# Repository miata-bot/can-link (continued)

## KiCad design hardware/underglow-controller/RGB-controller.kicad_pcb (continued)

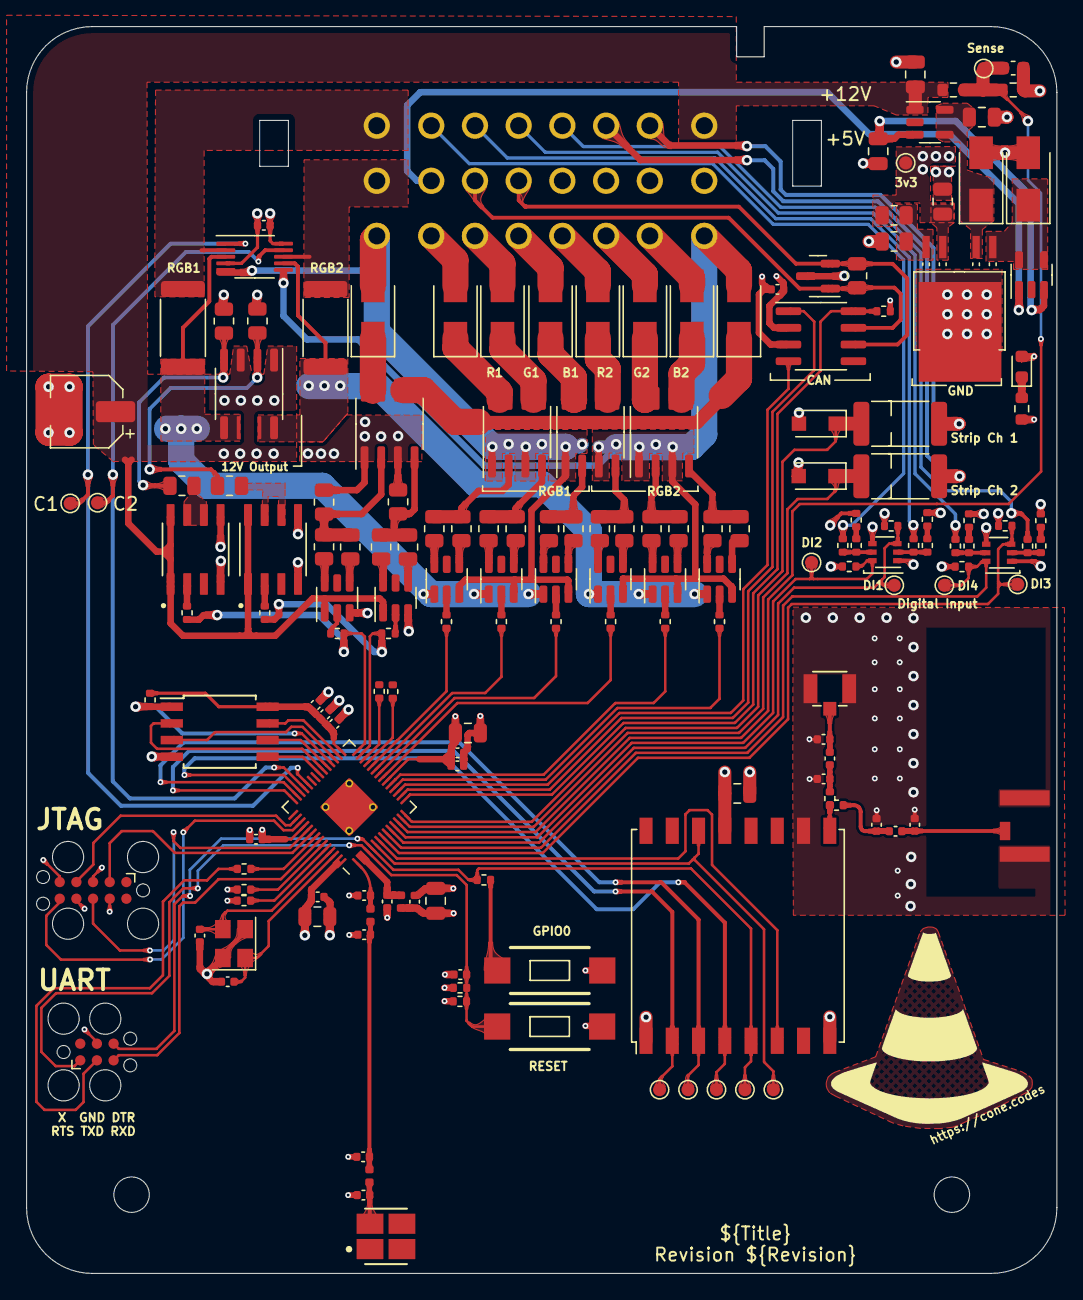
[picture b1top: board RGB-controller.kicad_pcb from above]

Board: 4 copper layers, 78.5 x 95.0 mm, 172 parts (0 on the bottom side), 140 nets.

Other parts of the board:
Enclosure_Bottom: Enclosure_Bottom
Enclosure_Top: Enclosure_Top

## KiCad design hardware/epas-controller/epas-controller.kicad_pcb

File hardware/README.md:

# Hardware Design

Here you'll find the hub for all the sub projects and KiCAD libraries.

| Folder | Description |
| -------| ----------- |
| [`underglow-controller`](/hardware/underglow-controller/README.md) | RGB controller board |
| - | - |
| [`library`](/hardware/library/README.md) | Library of KiCAD Parts |

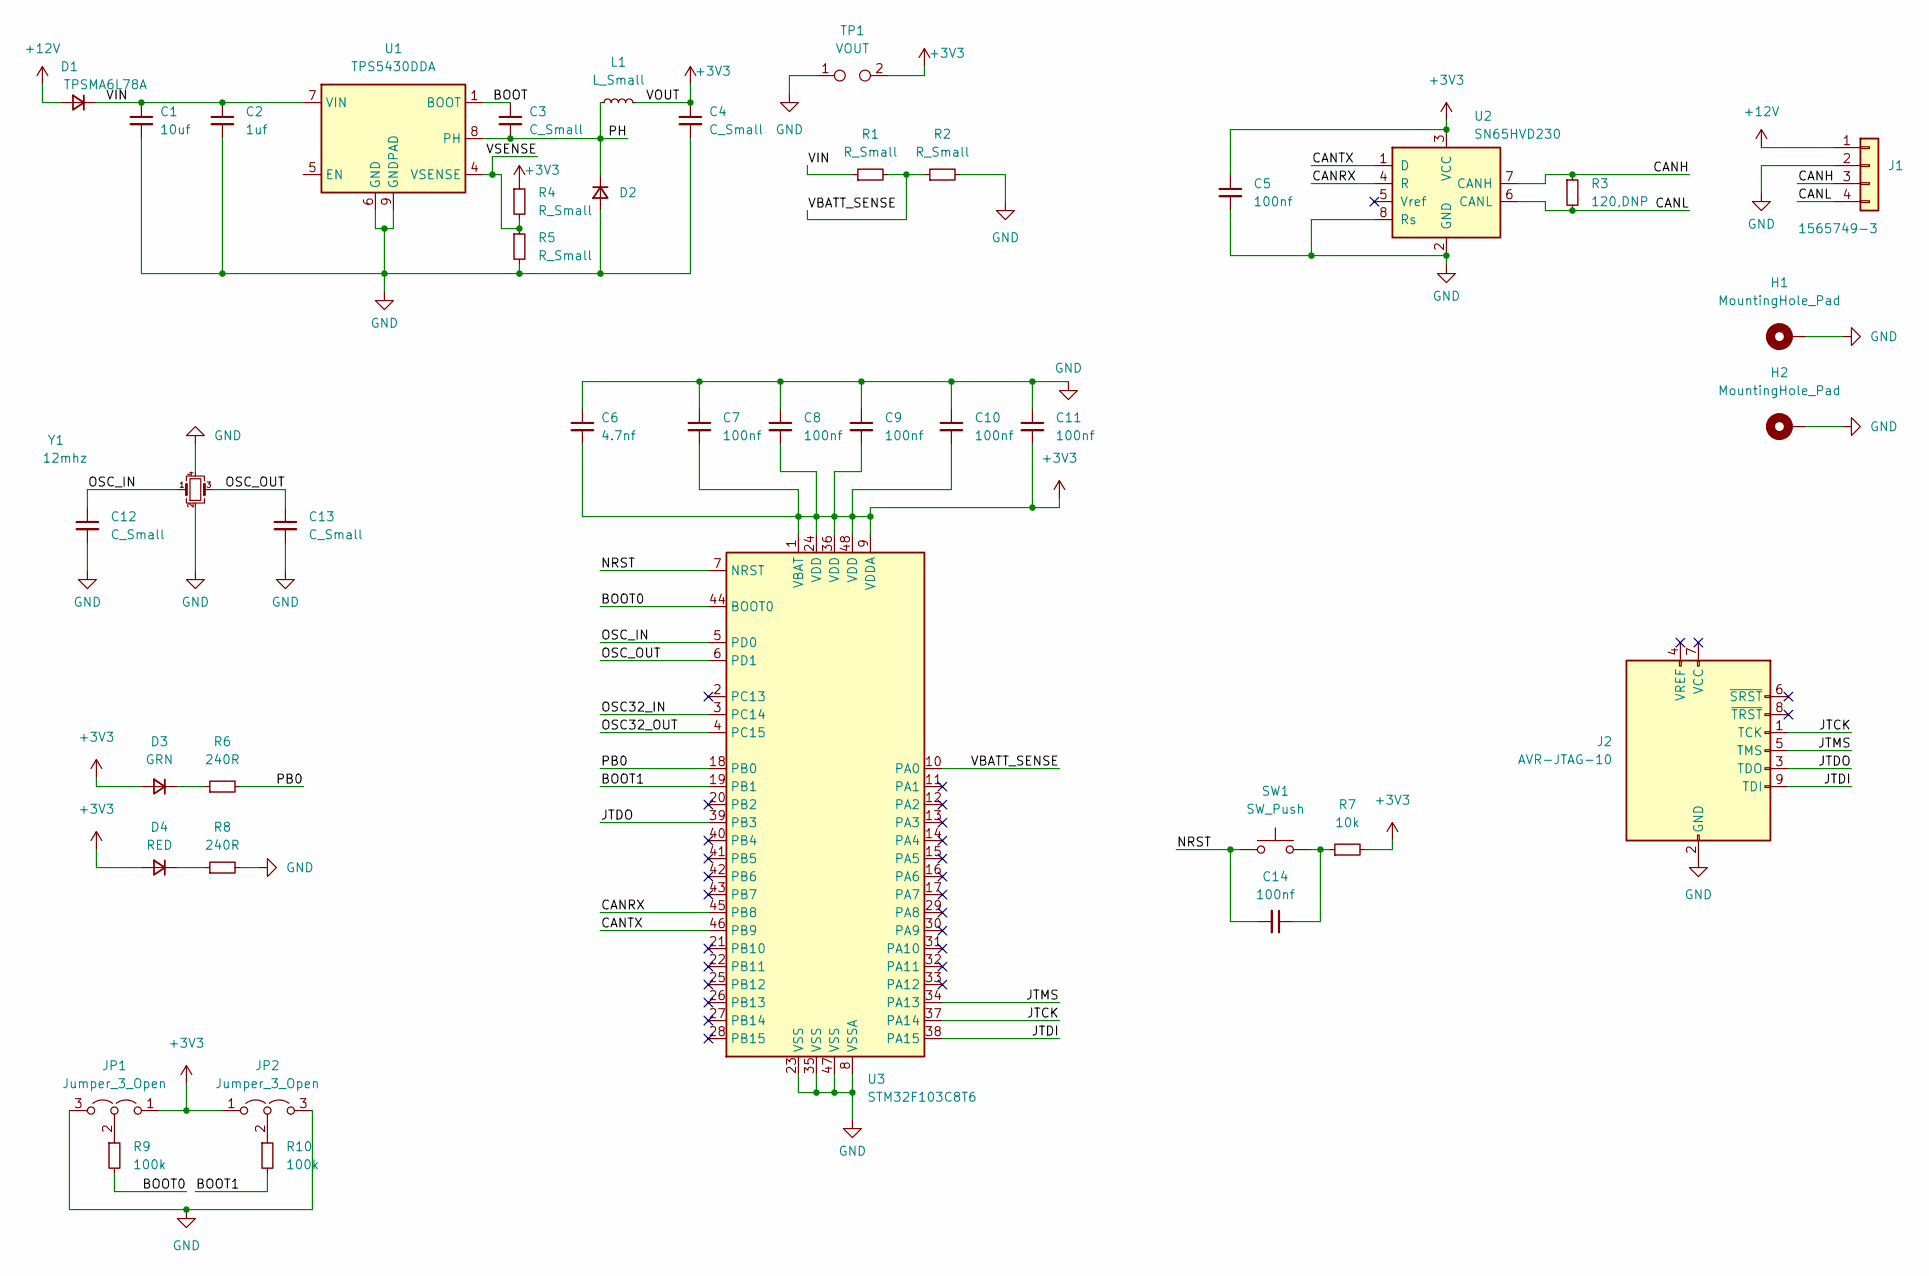
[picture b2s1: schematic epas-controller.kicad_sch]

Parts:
C1: 10uf; C_0805_2012Metric
C2: 1uf; C_0805_2012Metric
C3, C4: C_Small; C_0805_2012Metric
C5, C7, C8, C9, C10, C11, C14: 100nf; C_0402_1005Metric
C6: 4.7nf; C_0805_2012Metric
C12, C13: C_Small; C_0402_1005Metric
D1: TPSMA6L78A; D_SMA; MPN TPSMA6L78A
D2: D_Small; D_SOD-123F; MPN CUHS15S30,H3F
D3: GRN; LED_0603_1608Metric
D4: RED; LED_0603_1608Metric
H1, H2: MountingHole_Pad; MountingHole_3.2mm_M3_Pad_Via
J1: 1565749-3
J2: AVR-JTAG-10; PinHeader_2x06_P1.27mm_Vertical_SMD
JP1, JP2: Jumper_3_Open; SolderJumper-3_P1.3mm_Open_Pad1.0x1.5mm_NumberLabels
L1: L_Small; L_Bourns-SRN6028
R1, R2, R4, R5: R_Small; R_0603_1608Metric
R3: 120,DNP; R_0805_2012Metric
R6, R8: 240R; R_0603_1608Metric
R7: 10k; R_0402_1005Metric
R9, R10: 100k; R_0402_1005Metric
SW1: SW_Push; SW_RS-032G05A3-SMRT
TP1: VOUT; TestPoint_2Pads_Pitch2.54mm_Drill0.8mm
U1: TPS5430DDA; TI_SO-PowerPAD-8_ThermalVias; LCSC C9864
U2: SN65HVD230; SOIC-8_3.9x4.9mm_P1.27mm
U3: STM32F103C8T6; LQFP-48_7x7mm_P0.5mm; LCSC STM32F103C8T6
Y1: 12mhz; Crystal_SMD_3225-4Pin_3.2x2.5mm; MPN 12MHz SMD Crystal Resonator 20pF ±10ppm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; LCSC C9002

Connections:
+3V3: C4.1, C5.1, C6.2, C7.2, C8.2, C9.2, C10.2, C11.2, D3.2 (A), D4.2 (A), JP1.1 (A), JP2.1 (A), L1.2, R4.1, R7.2, TP1.2, U2.3 (VCC), U3.1 (VBAT), U3.9 (VDDA), U3.24 (VDD), U3.36 (VDD), U3.48 (VDD)
+12V: D1.2 (A), J1.1
/BOOT: C3.1, U1.1 (BOOT)
/BOOT0: R9.2, U3.44 (BOOT0)
/BOOT1: R10.2, U3.19 (PB1)
/CANH: J1.3, R3.1, U2.7 (CANH)
/CANL: J1.4, R3.2, U2.6 (CANL)
/CANRX: U2.4 (R), U3.45 (PB8)
/CANTX: U2.1 (D), U3.46 (PB9)
/JTCK: J2.1 (TCK), U3.37 (PA14)
/JTDI: J2.9 (TDI), U3.38 (PA15)
/JTDO: J2.3 (TDO), U3.39 (PB3)
/JTMS: J2.5 (TMS), U3.34 (PA13)
/NRST: C14.2, SW1.1, U3.7 (NRST)
/OSC32_IN: U3.3 (PC14)
/OSC32_OUT: U3.4 (PC15)
/OSC_IN: C12.1, U3.5 (PD0), Y1.1
/OSC_OUT: C13.1, U3.6 (PD1), Y1.3
/PB0: R6.2, U3.18 (PB0)
/PH: C3.2, D2.1 (K), L1.1, U1.8 (PH)
/VBATT_SENSE: R1.2, R2.1, U3.10 (PA0)
/VIN: C1.1, C2.1, D1.1 (K), R1.1, U1.7 (VIN)
/VSENSE: R4.2, R5.1, U1.4 (VSENSE)
GND: C1.2, C2.2, C4.2, C5.2, C6.1, C7.1, C8.1, C9.1, C10.1, C11.1, C12.2, C13.2, D2.2 (A), H1.1, H2.1, J1.2, J2.2 (GND), J2.10 (GND), JP1.3 (B), JP2.3 (B), R2.2, R5.2, R8.2, TP1.1, U1.6 (GND), U1.9 (GNDPAD), U2.2 (GND), U2.8 (Rs), U3.8 (VSSA), U3.23 (VSS), U3.35 (VSS), U3.47 (VSS), Y1.2, Y1.4
unnamed: C14.1, R7.1, SW1.2
unnamed: D3.1 (K), R6.1
unnamed: D4.1 (K), R8.1
unnamed: JP1.2 (C), R9.1
unnamed: JP2.2 (C), R10.1

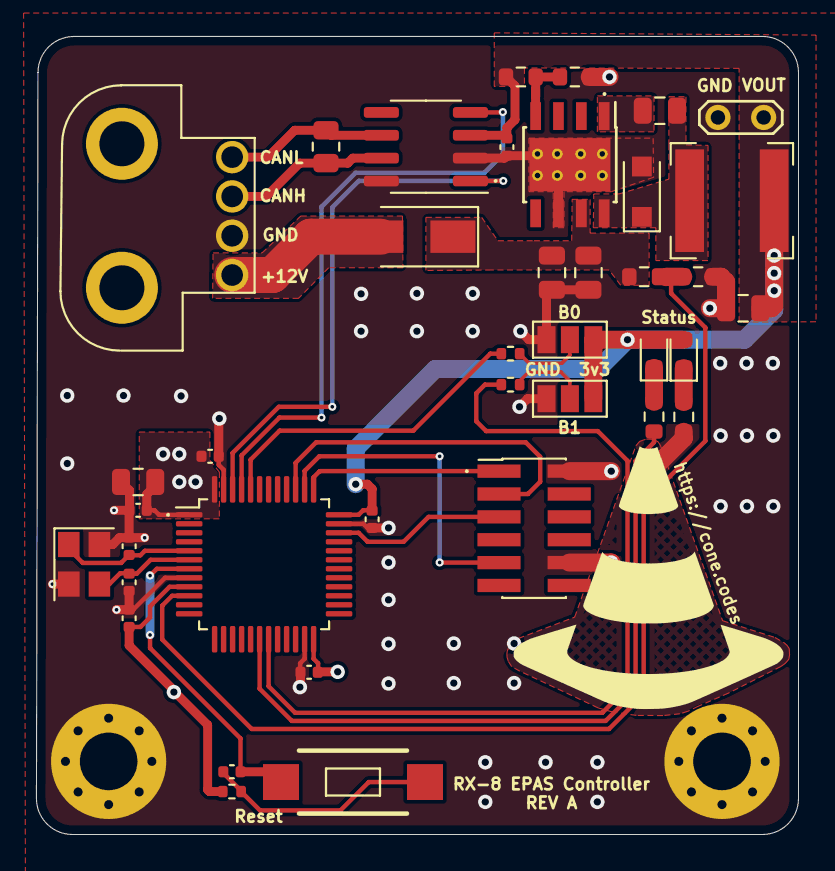
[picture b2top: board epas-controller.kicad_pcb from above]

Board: 2 copper layers, 42.3 x 44.3 mm, 41 parts (0 on the bottom side), 27 nets.

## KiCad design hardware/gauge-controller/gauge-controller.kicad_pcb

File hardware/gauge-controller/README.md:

# CAN Multi-Gauge Controller

Device designed to display information from an ECU?

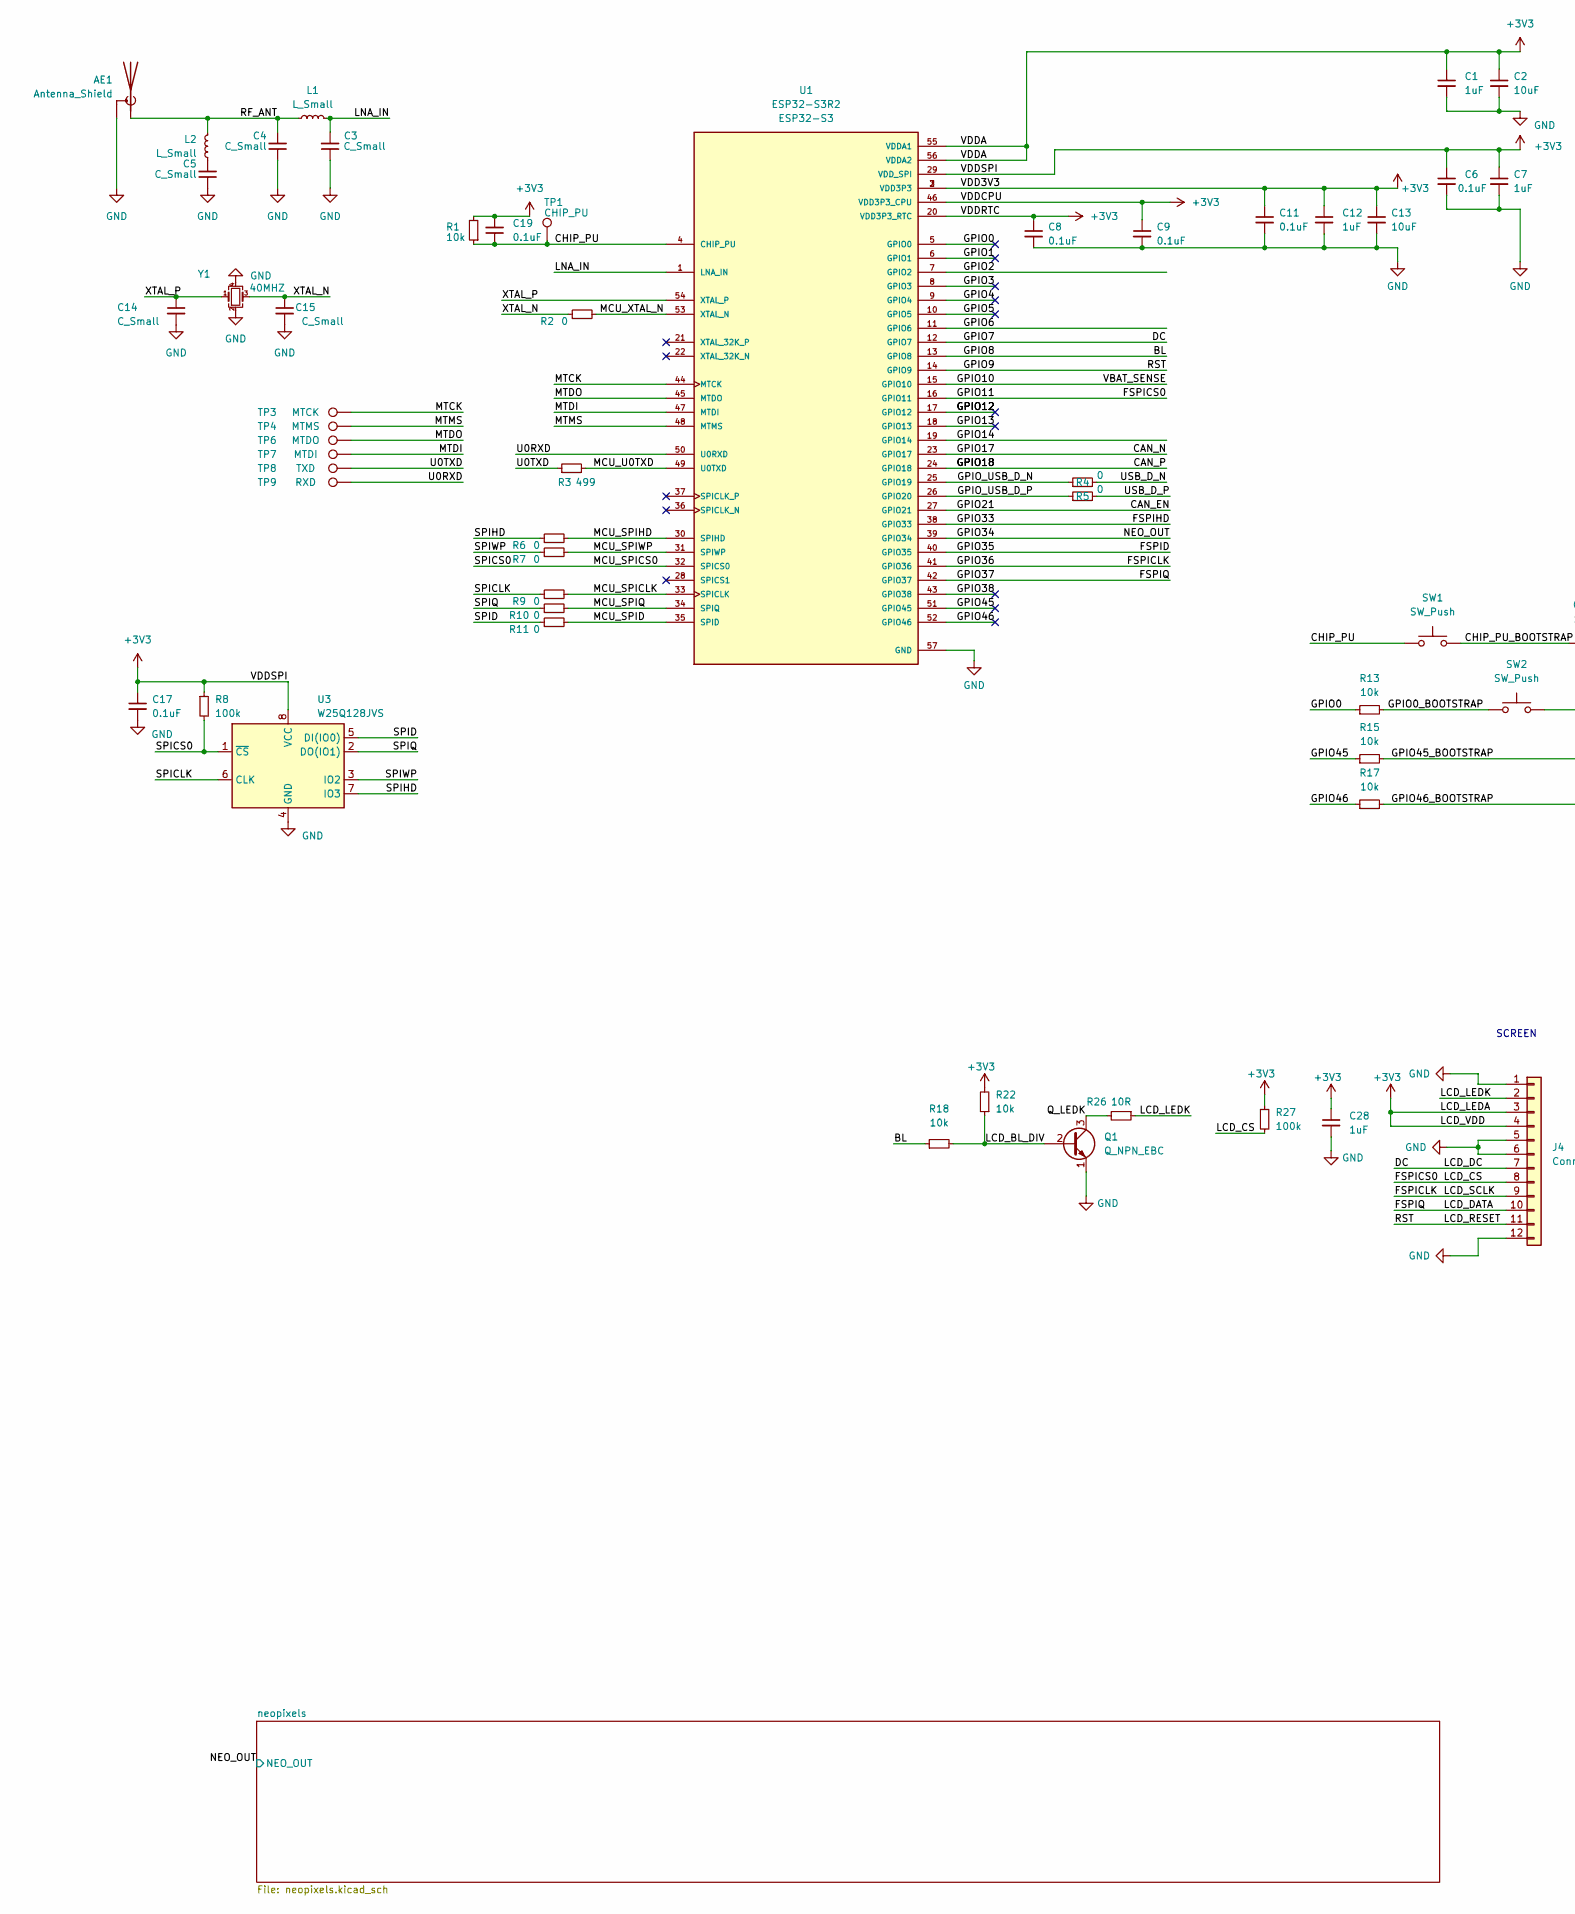
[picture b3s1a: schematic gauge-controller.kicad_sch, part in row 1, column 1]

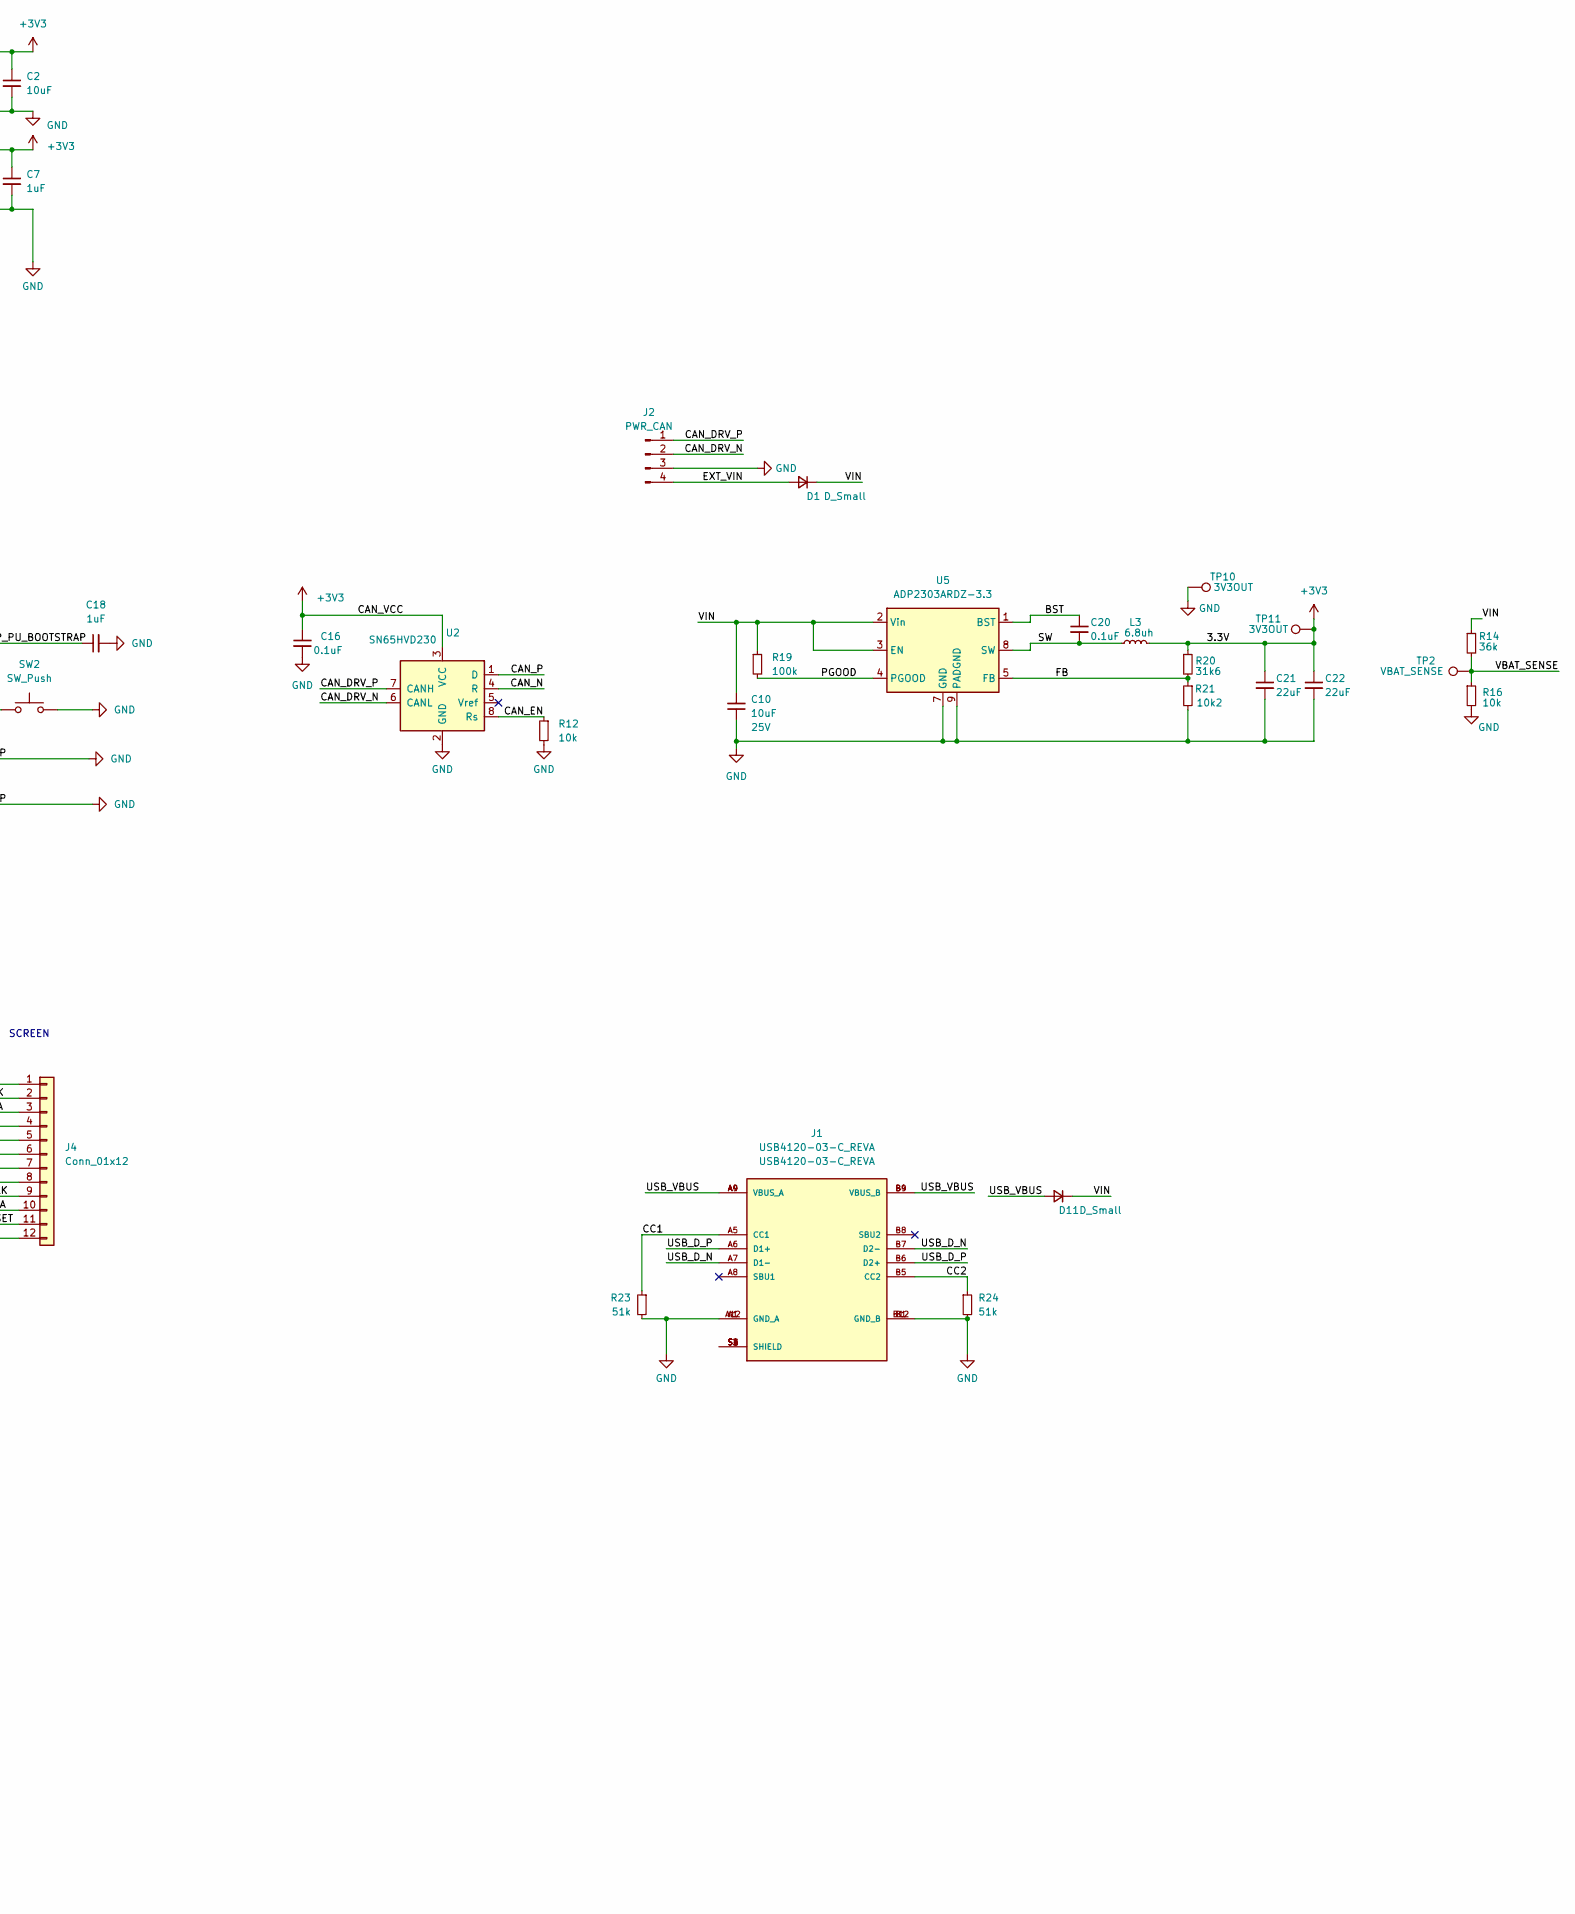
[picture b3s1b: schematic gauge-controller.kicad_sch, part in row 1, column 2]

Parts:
AE1: Antenna_Shield; Johanson_2450AT18x100
C1, C7, C12, C18, C28: 1uF; C_0402_1005Metric
C2, C13: 10uF; C_0402_1005Metric
C3, C4, C5, C14, C15: C_Small; C_0402_1005Metric
C6, C8, C9, C11, C16, C17, C19: 0.1uF; C_0402_1005Metric
C10: 10uF; C_0805_2012Metric; VOLTAGE 25V
C20: 0.1uF; C_0805_2012Metric
C21, C22: 22uF; C_0805_2012Metric
D1, D11: D_Small; D_SOD-123F
J1: USB4120-03-C_REVA; GCT_USB4120-03-C_REVA; MPN USB4120-03-C_REVA
J2: PWR_CAN; JST_GH_BM04B-GHS-TBT_1x04-1MP_P1.25mm_Vertical
J4: Conn_01x12; GC9A01_disp
L1, L2: L_Small; L_0402_1005Metric
L3: 6.8uh; L_Bourns-SRN6028; MPN SRN6028-6R8M
Q1: Q_NPN_EBC; TSOT-23
R1, R12, R13, R15, R16, R17, R18, R22: 10k; R_0402_1005Metric
R2, R4, R5, R6, R7, R9, R10, R11: 0; R_0402_1005Metric
R3: 499; R_0402_1005Metric
R8, R27: 100k; R_0402_1005Metric
R14: 36k; R_0402_1005Metric
R19: 100k; R_0603_1608Metric
R20: 31k6; R_0603_1608Metric
R21: 10k2; R_0603_1608Metric
R23, R24: 51k; R_0402_1005Metric
R26: 10R; R_0402_1005Metric
SW1, SW2: SW_Push; SW_RS-032G05A3-SMRT
TP1: CHIP_PU; TestPoint_Pad_D1.0mm
TP2: VBAT_SENSE; TestPoint_Pad_D1.0mm
TP3: MTCK; TestPoint_Pad_D1.0mm
TP4: MTMS; TestPoint_Pad_D1.0mm
TP6: MTDO; TestPoint_Pad_D1.0mm
TP7: MTDI; TestPoint_Pad_D1.0mm
TP8: TXD; TestPoint_Pad_D1.0mm
TP9: RXD; TestPoint_Pad_D1.0mm
TP10, TP11: 3V3OUT; TestPoint_Pad_D1.0mm
U1: ESP32-S3R2; QFN-56; MPN ESP32-S3
U2: SN65HVD230; SOIC-8_3.9x4.9mm_P1.27mm; MPN SN65HVD230D
U3: W25Q128JVS; SOIC-8W_5.3x5.3mm_P1.27mm; JLCPCB C97521
U5: ADP2303ARDZ-3.3; SOIC-8-1EP_3.9x4.9mm_P1.27mm_EP2.29x3mm_ThermalVias
Y1: 40MHZ; Crystal_SMD_3225-4Pin_3.2x2.5mm; JLCPCB C9010

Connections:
+3V3: C1.1, C2.1, C6.1, C7.1, C8.1, C9.1, C11.1, C12.1, C13.1, C16.1, C17.1, C19.2, C21.1, C22.1, C28.1, J4.3, J4.4, L3.2, R1.2, R8.1, R20.1, R22.2, R27.1, TP11.1, U1.2 (VDD3P3), U1.3 (VDD3P3), U1.20 (VDD3P3_RTC), U1.29 (VDD_SPI), U1.46 (VDD3P3_CPU), U1.55 (VDDA1), U1.56 (VDDA2), U2.3 (VCC), U3.8 (VCC); also elsewhere on the board
/BL: R18.1, U1.13 (GPIO8)
/BST: C20.1, U5.1 (BST)
/CAN_DRV_N: J2.2, U2.6 (CANL)
/CAN_DRV_P: J2.1, U2.7 (CANH)
/CAN_EN: R12.1, U1.27 (GPIO21), U2.8 (Rs)
/CAN_N: U1.23 (GPIO17), U2.4 (R)
/CAN_P: U1.24 (GPIO18), U2.1 (D)
/CC1: J1.A5 (CC1), R23.1
/CC2: J1.B5 (CC2), R24.1
/CHIP_PU: C19.1, R1.1, SW1.1, TP1.1, U1.4 (CHIP_PU)
/CHIP_PU_BOOTSTRAP: C18.1, SW1.2
/DC: J4.7, U1.12 (GPIO7)
/EXT_VIN: D1.2 (A), J2.4
/FB: R20.2, R21.1, U5.5 (FB)
/FSPICLK: J4.9, U1.41 (GPIO36)
/FSPICS0: J4.8, R27.2, U1.16 (GPIO11)
/FSPID: U1.40 (GPIO35)
/FSPIHD: U1.38 (GPIO33)
/FSPIQ: J4.10, U1.42 (GPIO37)
/GPIO0: R13.1, U1.5 (GPIO0)
/GPIO0_BOOTSTRAP: R13.2, SW2.1
/GPIO1: U1.6 (GPIO1)
/GPIO2: U1.7 (GPIO2)
/GPIO3: U1.8 (GPIO3)
/GPIO4: U1.9 (GPIO4)
/GPIO5: U1.10 (GPIO5)
/GPIO6: U1.11 (GPIO6)
/GPIO9: J4.11, U1.14 (GPIO9)
/GPIO10: R14.2, R16.1, TP2.1, U1.15 (GPIO10)
/GPIO12: U1.17 (GPIO12)
/GPIO13: U1.18 (GPIO13)
/GPIO14: U1.19 (GPIO14)
/GPIO34: U1.39 (GPIO34); also elsewhere on the board
/GPIO38: U1.43 (GPIO38)
/GPIO45: R15.1, U1.51 (GPIO45)
/GPIO46: R17.1, U1.52 (GPIO46)
/GPIO_USB_D_N: R4.1, U1.25 (GPIO19)
/GPIO_USB_D_P: R5.1, U1.26 (GPIO20)
/LCD_BL_DIV: Q1.2 (B), R18.2, R22.1
/LCD_LEDK: J4.2, R26.1
/LNA_IN: C3.2, L1.1, U1.1 (LNA_IN)
/MCU_SPICLK: R9.2, U1.33 (SPICLK)
/MCU_SPICS0: R8.2, U1.32 (SPICS0), U3.1 (~CS)
/MCU_SPID: R11.2, U1.35 (SPID)
/MCU_SPIHD: R6.2, U1.30 (SPIHD)
/MCU_SPIQ: R10.2, U1.34 (SPIQ)
/MCU_SPIWP: R7.2, U1.31 (SPIWP)
/MCU_U0TXD: R3.2, U1.49 (U0TXD)
/MCU_XTAL_N: R2.2, U1.53 (XTAL_N)
/MTCK: TP3.1, U1.44 (MTCK)
/MTDI: TP7.1, U1.47 (MTDI)
/MTDO: TP6.1, U1.45 (MTDO)
/MTMS: TP4.1, U1.48 (MTMS)
/PGOOD: R19.2, U5.4 (PGOOD)
/Q_LEDK: Q1.3 (C), R26.2
/RF_ANT: AE1.1 (A), C4.2, L1.2, L2.1
/SPICLK: R9.1, U3.6 (CLK)
/SPID: R11.1, U3.5 (DI(IO0))
/SPIHD: R6.1, U3.7 (IO3)
/SPIQ: R10.1, U3.2 (DO(IO1))
/SPIWP: R7.1, U3.3 (IO2)
/SW: C20.2, L3.1, U5.8 (SW)
/U0RXD: TP9.1, U1.50 (U0RXD)
/U0TXD: R3.1, TP8.1
/USB_D_N: J1.A7 (D1-), J1.B7 (D2-), R4.2
/USB_D_P: J1.A6 (D1+), J1.B6 (D2+), R5.2
/USB_VBUS: D11.2 (A), J1.A4 (VBUS_A), J1.A9 (VBUS_A), J1.B4 (VBUS_B), J1.B9 (VBUS_B)
/VIN: C10.2, D1.1 (K), D11.1 (K), R14.1, R19.1, U5.2 (Vin), U5.3 (EN)
/XTAL_N: C15.1, R2.1, Y1.3
/XTAL_P: C14.1, U1.54 (XTAL_P), Y1.1
GND: AE1.2 (Shield), C1.2, C2.2, C3.1, C4.1, C5.1, C6.2, C7.2, C8.2, C9.2, C10.1, C11.2, C12.2, C13.2, C14.2, C15.2, C16.2, C17.2, C18.2, C21.2, C22.2, C28.2, J1.A1 (GND_A), J1.A12 (GND_A), J1.B1 (GND_B), J1.B12 (GND_B), J2.3, J4.1, J4.5, J4.6, J4.12, Q1.1 (E), R12.2, R15.2, R16.2, R17.2, R21.2, R23.2, R24.2, SW2.2, TP10.1, U1.57 (GND), U2.2 (GND), U3.4 (GND), U5.7 (GND), U5.9 (PADGND), Y1.2, Y1.4; also elsewhere on the board
unnamed: C5.2, L2.2
unnamed: J1.S1 (SHIELD), J1.S2 (SHIELD), J1.S3 (SHIELD), J1.S4 (SHIELD)

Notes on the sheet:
SCREEN

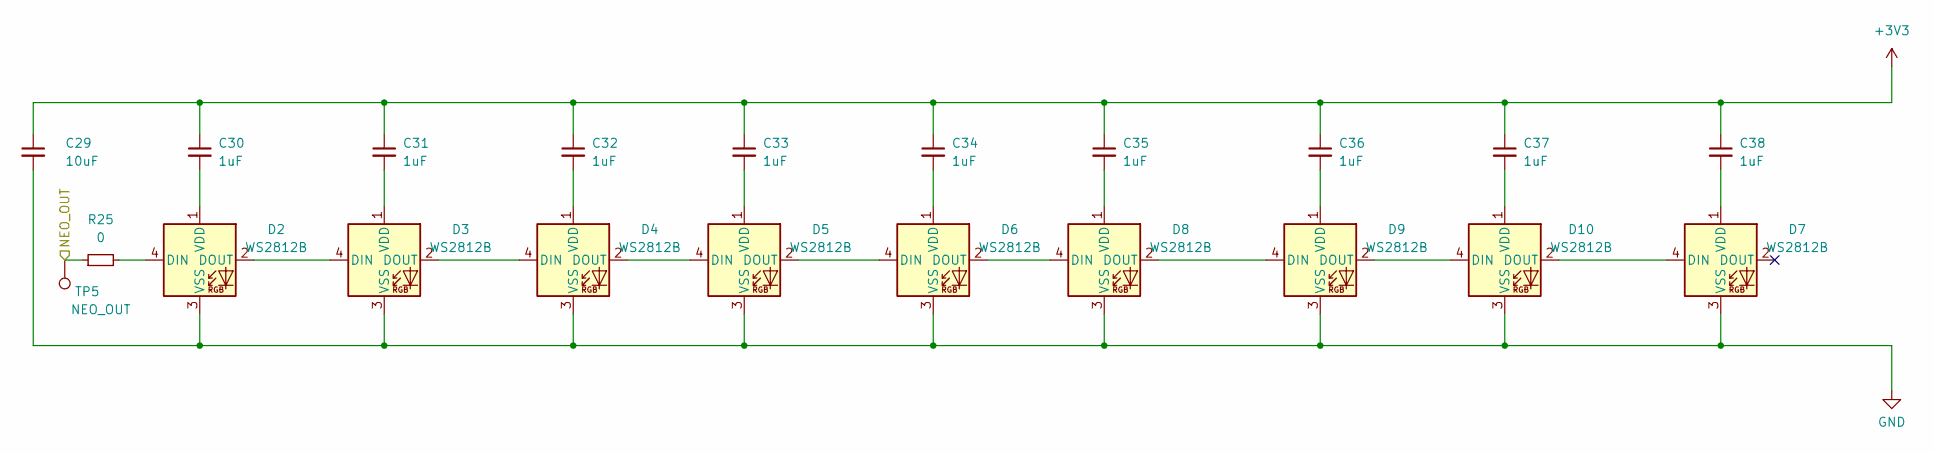
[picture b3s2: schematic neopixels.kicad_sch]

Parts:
C29: 10uF; C_0402_1005Metric
C30, C31, C32, C33, C34, C35, C36, C37, C38: 1uF; C_0402_1005Metric
D2, D3, D4, D5, D6, D7, D8, D9, D10: WS2812B; LED_WS2812B_PLCC4_5.0x5.0mm_P3.2mm
R25: 0; R_0402_1005Metric
TP5: NEO_OUT; TestPoint_Pad_D1.0mm

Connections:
+3V3: C29.1, C30.1, C31.1, C32.1, C33.1, C34.1, C35.1, C36.1, C37.1, C38.1; also elsewhere on the board
/GPIO34: R25.1, TP5.1; also elsewhere on the board
GND: C29.2, D2.3 (VSS), D3.3 (VSS), D4.3 (VSS), D5.3 (VSS), D6.3 (VSS), D7.3 (VSS), D8.3 (VSS), D9.3 (VSS), D10.3 (VSS); also elsewhere on the board
unnamed: C30.2, D2.1 (VDD)
unnamed: C31.2, D3.1 (VDD)
unnamed: C32.2, D4.1 (VDD)
unnamed: C33.2, D5.1 (VDD)
unnamed: C34.2, D6.1 (VDD)
unnamed: C35.2, D8.1 (VDD)
unnamed: C36.2, D9.1 (VDD)
unnamed: C37.2, D10.1 (VDD)
unnamed: C38.2, D7.1 (VDD)
unnamed: D2.2 (DOUT), D3.4 (DIN)
unnamed: D2.4 (DIN), R25.2
unnamed: D3.2 (DOUT), D4.4 (DIN)
unnamed: D4.2 (DOUT), D5.4 (DIN)
unnamed: D5.2 (DOUT), D6.4 (DIN)
unnamed: D6.2 (DOUT), D8.4 (DIN)
unnamed: D8.2 (DOUT), D9.4 (DIN)
unnamed: D7.4 (DIN), D10.2 (DOUT)
unnamed: D9.2 (DOUT), D10.4 (DIN)

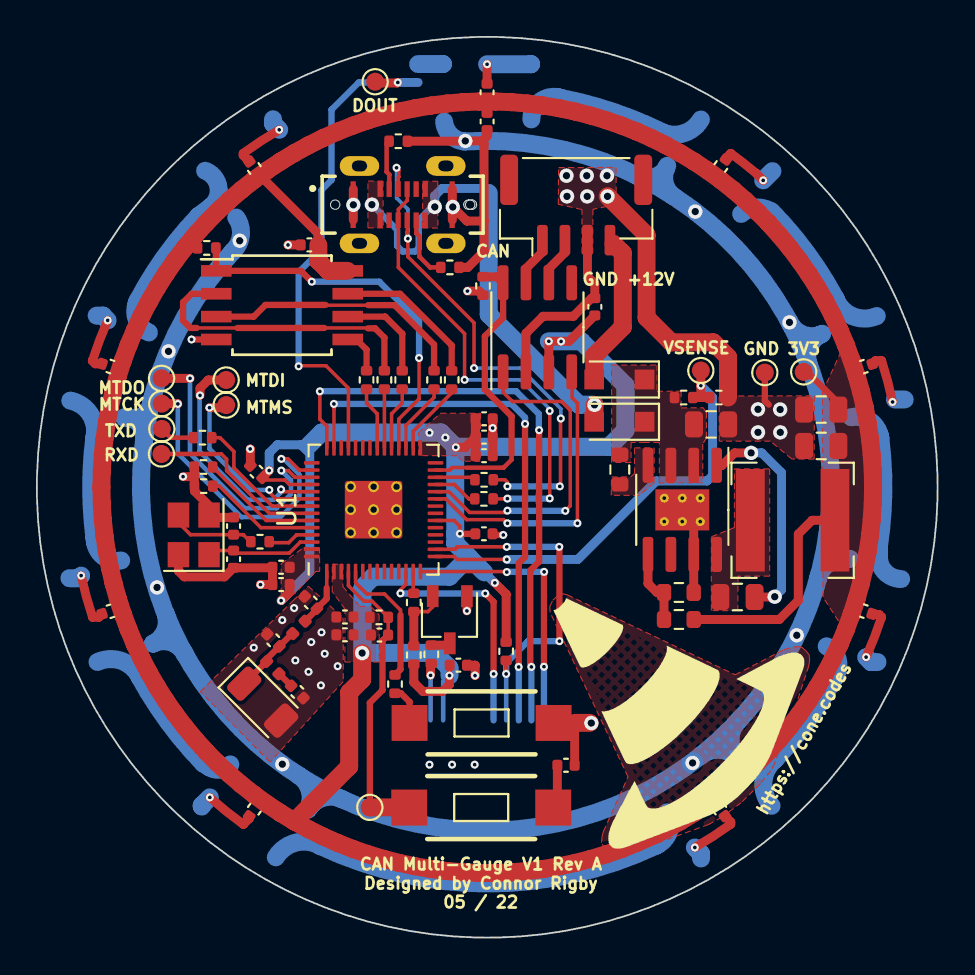
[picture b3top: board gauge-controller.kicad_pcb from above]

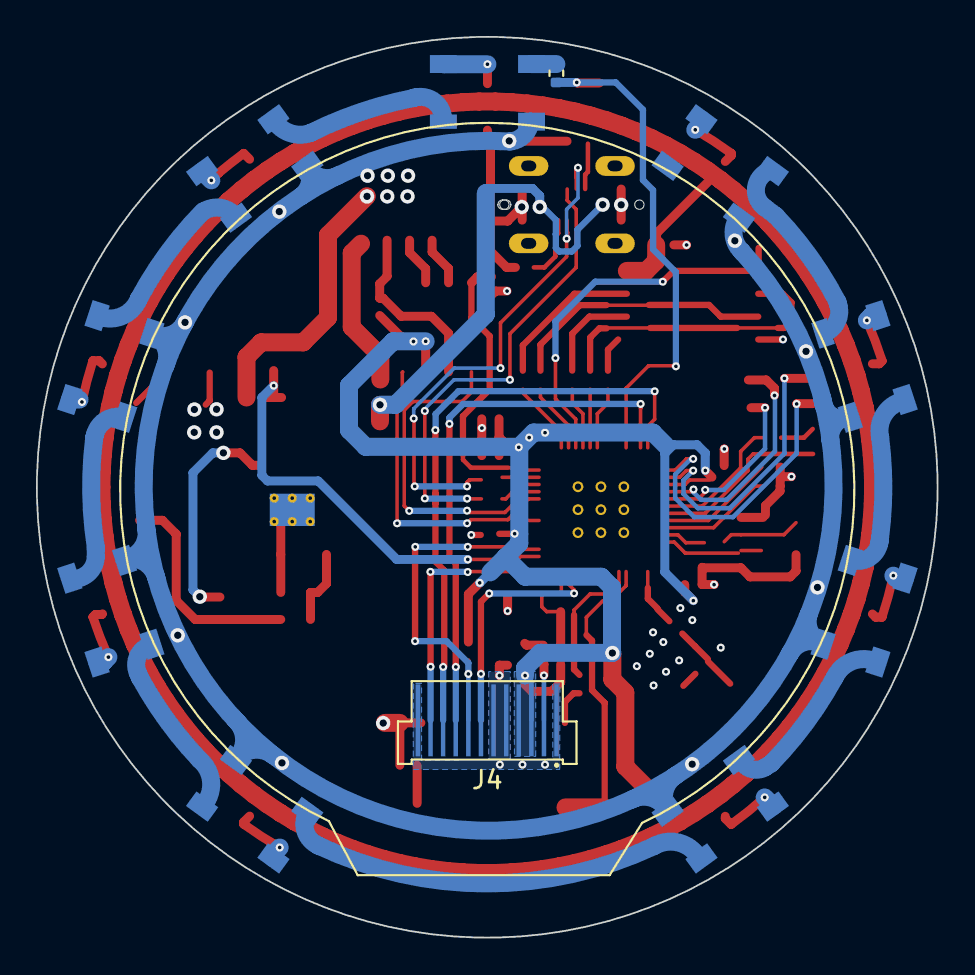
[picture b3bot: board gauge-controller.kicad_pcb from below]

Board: 4 copper layers, 50.0 x 50.0 mm, 97 parts (11 on the bottom side), 80 nets.
